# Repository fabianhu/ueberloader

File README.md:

# ueberloader

A RC Battery Charger with high power output and quite small footprint.

Capable of charging 6S at 10A with 24V power supply.

Core component is a "full bridge converter" which is controlled via software.

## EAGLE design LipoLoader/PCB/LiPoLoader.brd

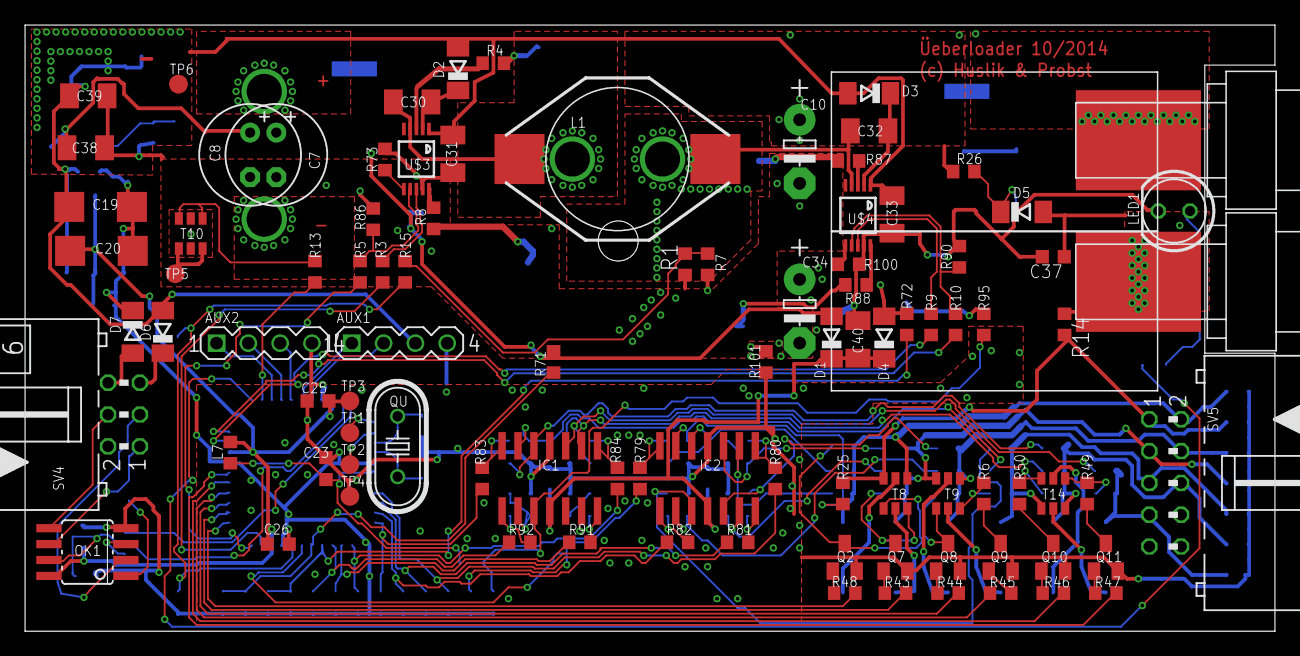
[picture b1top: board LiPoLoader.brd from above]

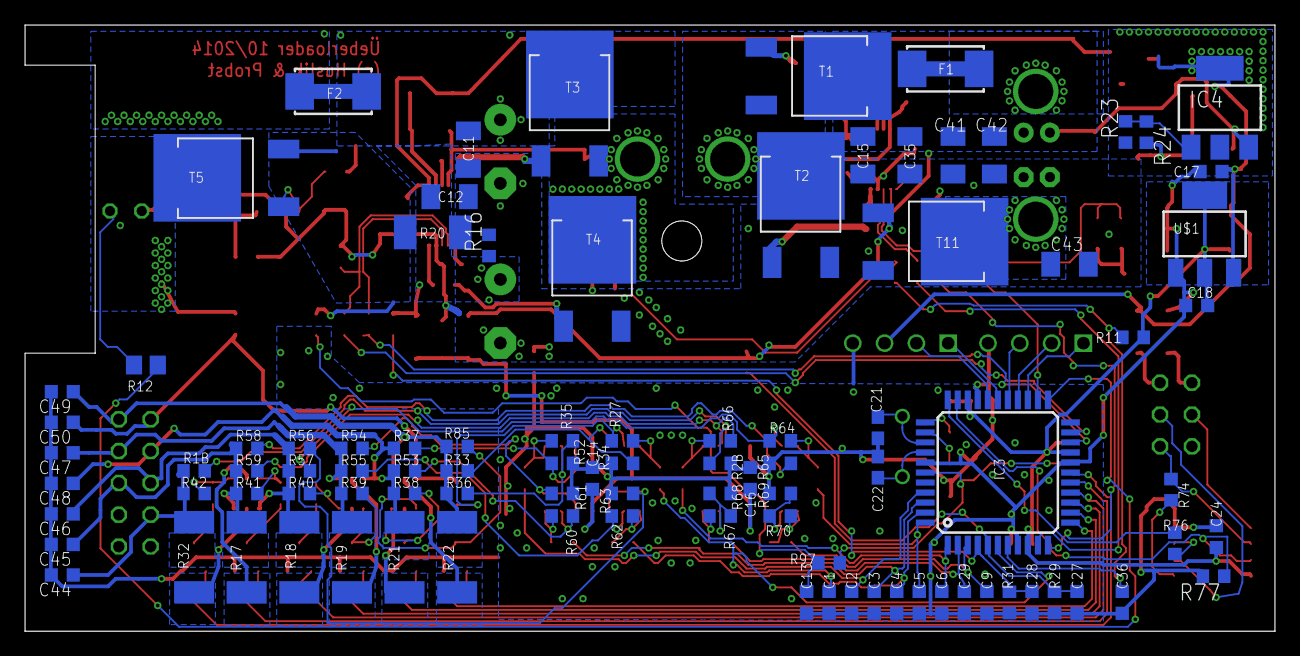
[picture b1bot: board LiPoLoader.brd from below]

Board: 2 copper layers, 99.8 x 48.4 mm, 195 parts (95 on the bottom side), 129 nets.

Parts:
AUX1: aux; MA04-1
AUX2: encoder; MA04-1
C1, C2, C3, C4, C5, C6, C9, C13, C14, C16, C17, C18, C23, C24, C25, C26, C27, C28, C29, C36, C37, C44, C45, C46, C47, C48, C49, C50: 100n; C0603K
C7, C8: 330µF / 25V; E3,5-8
C10, C34: 1000µF/35V; E5-13-L
C11, C15, C30, C31, C32, C33, C38, C39, C40: 1u; C1206K
C12, C35, C41, C42, C43: 10µF; C1206K
C19, C20: 100u Tan; SMC_C
C21, C22: 10p; C0603
COIL1, COIL2: SOLPAD3MM
D1, D2, D3, D4, D6, D7: LL43-GS08; SOD80C
D5: 15V BZT55C15; SOD80C
F1, F2: Fuse 10A; WSC2515
IC1, IC2: LM224D; SO14
IC3: AVR_XMEGA_A4_44A; TQFP44
IC4: LM317MSTT3; SOT223
L1: COILCRAFT_D333; D333
L7: 27nH; R0603
LED1: LED5MM
OK1: ILD217; SOIC08
Q2, Q7, Q8, Q9, Q10, Q11: BC817-25SMD; SOT23-BEC
QU: 16MHz; HC49U-V
R1, R11, R14: 2k2; R0603
R1B, R25, R33, R36, R37, R53, R54, R55, R56, R57, R58, R59: 43k - 0.1%; R0603
R2B, R27, R34, R35, R52, R60, R61, R62, R63, R64, R65, R66: 20k - 0.1%; R0603
R3, R5, R9, R10, R13, R15, R101: 0R; R0603
R4, R8, R87, R88: 10; R0603
R6, R16, R38, R39, R40, R41, R42, R49, R50, R73, R79, R80, R81, R82, R83, R84, R85, R86, R90, R91, R92, R100: 10k; R0603
R7: NB12K00103JBB; R0603
R12: 330; R0805
R17, R18, R19, R21, R22, R32: 10; R2512
R20: 0.005R; R2010
R23: 470; R0603
R24: 3300; R0603
R26: 100k; R0603
R29, R31, R67: 10k - 0.1%; R0603
R43, R44, R45, R46, R47, R48, R77: 4k7; R0603
R68, R69, R95: 2k - 0.1%; R0603
R70: 36k - 0.1%; R0603
R71, R72, R97: 120k - 0.1%; R0603
R74, R76: 820; R0603
SUPP+: SOLPAD3MM
SUPP-: SOLPAD3MM
SV4: comm; ML6L
SV5: ML10L
T1, T2, T3, T4, T5, T11: MOSFET-NIRLR8743; DPAK
T8, T9, T14: QS6J1=FDC6312P; SUPERSOT-6
T10: FDC6401N; SUPERSOT-6
TP1, TP2, TP3, TP4, TP5, TP6: TPTP15R; TP15R
U$1: LM1117; SOT223
U$2: GEH_FISCHER_AKG55XX100_BODEN
U$3, U$4: LM5106; MSOP10W
U$5, U$6: BUCHSE4MM; BUCHSE4MML

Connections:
0V: C7.-, C8.-, C10.-, C11.1, C12.2, C15.1, C31.1, C33.1, C34.-, C35.2, C37.2, C38.1, C39.1, C40.1, C41.2, C42.2, C43.2, LED1.K, R1.1, R7.1, R16.2, R20.1, R24.2, R73.2, R86.2, R90.2, R100.2, R101.2, T2.3, T4.3, T10.P$2, T10.P$5, T11.3, U$3.9, U$4.9
+3V3: C18.2, C20.+, C24.2, C25.2, C26.2, IC3.9, IC3.19, IC3.31, L7.2, OK1.8, R11.2, TP3.TP, U$1.MID, U$1.TAP
+12V: AUX1.3, C17.2, C19.+, C31.2, C33.2, C39.2, D2.A, D3.A, D6.A, IC4.4, R23.1, TP6.TP, U$1.RIGHT, U$3.1, U$4.1
+UB: C10.+, C11.2, C12.1, C34.+, D4.A, F2.1, R16.1, R26.1, R72.1, T3.4
AVCC: C23.2, IC3.39, L7.1, R97.1
BALANCE1: IC3.12, R48.1
BALANCE2: IC3.13, R43.1
BALANCE3: IC3.14, R44.1
BALANCE4: IC3.15, R45.1
BALANCE5: IC3.16, R46.1
BALANCE6: IC3.17, R47.1
BATT-: C37.1, D5.A, R14.1, T5.4, U$6.P$1
BATT-B: R20.2, R95.2, T5.3
BUS_RX: OK1.2, SV4.3
BUS_SUPP: OK1.6, R74.1, SV4.1
BUS_TX: OK1.5, SV4.4
CELL1: C49.1, R22.1, R33.1, R36.1, R85.2, SV5.2, T8.P$4
CELL2: C48.1, R21.1, R37.1, R38.2, R53.1, SV5.3, T9.P$6
CELL3: C47.1, R19.1, R39.2, R54.1, R55.1, SV5.4, T9.P$4
CELL4: C46.1, R18.1, R40.2, R56.1, R57.1, SV5.5, T14.P$4
CELL5: C45.1, R17.1, R41.2, R58.1, R59.1, SV5.6, T14.P$6
CELL6: C44.1, R1B.1, R32.1, R42.2, SV5.7
CELLGND: C50.1, R14.2, R25.1, SV5.1, T8.P$6
GND: AUX1.4, AUX2.4, C1.1, C2.1, C3.1, C4.1, C5.1, C6.1, C9.1, C13.1, C14.1, C16.1, C17.1, C18.1, C19.-, C20.-, C21.1, C22.1, C23.1, C24.1, C25.1, C26.1, C27.1, C28.1, C29.1, C36.1, C44.2, C45.2, C46.2, C47.2, C48.2, C49.2, C50.2, D7.C, IC1.11, IC2.11, IC3.8, IC3.18, IC3.30, IC3.38, IC3.40, OK1.4, Q2.E, Q7.E, Q8.E, Q9.E, Q10.E, Q11.E, R2B.1, R29.2, R31.2, R34.1, R52.1, R61.1, R63.1, R65.1, R68.2, R69.2, R77.2, R101.1, TP4.TP, U$1.LEFT
I_ACT_HI: C9.2, IC3.3, R92.1
I_ACT_LOW: C29.2, IC3.2, R91.1
I_RAW_HI_R: C13.2, IC1.3, R95.1, R97.2
LED1: IC3.23, R12.1
MISO: AUX2.2, IC3.26
MOSI: AUX2.1, IC3.25
unnamed: IC1.10, R1B.2, R2B.2
unnamed: IC1.12, R58.2, R65.2
unnamed: IC1.9, R59.2, R66.2
unnamed: R8.1, T2.1
unnamed: R87.2, U$4.3
unnamed: IC1.13, R57.2, R64.2
unnamed: IC1.6, R67.2, R68.1
unnamed: R100.1, U$4.6
unnamed: OK1.3, R76.1
unnamed: IC2.3, R56.2, R63.2
unnamed: IC2.2, R55.2, R62.2
unnamed: R88.1, T4.1
unnamed: F2.2, U$5.P$1
unnamed: R4.2, U$3.3
unnamed: IC2.5, R54.2, R61.2
unnamed: IC2.6, R53.2, R60.2
unnamed: IC2.12, R33.2, R34.2
unnamed: D7.A, SV4.6
unnamed: LED1.A, R12.2
unnamed: IC2.10, R37.2, R52.2
unnamed: IC2.9, R35.2, R36.2
unnamed: IC2.13, R25.2, R27.2
unnamed: OK1.1, R74.2
unnamed: C32.1, COIL2.P$1, L1.2, T3.3, T4.4, U$4.4
unnamed: R22.2, T8.P$5
unnamed: IC4.1, R23.2, R24.1
unnamed: IC1.2, R69.1, R70.2
unnamed: IC1.8, R66.1, R84.2
unnamed: C21.2, IC3.36, QU.2
unnamed: C22.2, IC3.37, QU.1
unnamed: T10.P$4, T10.P$6, TP5.TP
unnamed: IC1.7, R67.1, R91.2
unnamed: C30.1, COIL1.P$1, L1.1, T1.3, T2.4, U$3.4
unnamed: F1.2, SUPP+.P$1
unnamed: D5.C, R26.2, T5.1
unnamed: Q8.C, R39.1, T9.P$1
unnamed: Q9.C, R6.1
unnamed: R5.2, R86.1, U$3.7
unnamed: R9.1, U$4.8
unnamed: R13.2, T10.P$1, T10.P$3
unnamed: R21.2, T8.P$2
unnamed: R19.2, T9.P$5
unnamed: IC1.14, R64.1, R83.2
unnamed: R18.2, T9.P$2
unnamed: R17.2, T14.P$2
unnamed: R32.2, T14.P$5
unnamed: Q2.C, R85.1, T8.P$1
unnamed: Q7.B, R43.2
unnamed: Q8.B, R44.2
unnamed: Q9.B, R45.2
unnamed: Q10.B, R46.2
unnamed: Q11.B, R47.2
unnamed: IC2.1, R62.1, R82.2
unnamed: R6.2, R40.1, T9.P$3
unnamed: R41.1, R50.2, T14.P$3
unnamed: R42.1, R49.2, T14.P$1
unnamed: Q7.C, R38.1, T8.P$3
unnamed: IC2.7, R60.1, R81.2
unnamed: Q11.C, R49.1
unnamed: Q10.C, R50.1
unnamed: IC2.8, R35.1, R80.2
unnamed: IC2.14, R27.1, R79.2
unnamed: R1.2, R7.2, R15.1
unnamed: R8.2, U$3.10
unnamed: R4.1, T1.1
unnamed: R3.2, U$3.8
unnamed: R73.1, U$3.6
unnamed: C30.2, D2.C, U$3.2
unnamed: IC1.1, R70.1, R92.2
unnamed: R88.2, U$4.10
unnamed: R87.1, T3.1
unnamed: R10.1, R90.1, U$4.7
unnamed: C32.2, D3.C, U$4.2
unnamed: D6.C, SV4.5
unnamed: Q2.B, R48.2
OPAMP_SUPP: C14.2, C16.2, C40.2, D1.C, D4.C, IC1.4, IC2.4
PDI_CLK: IC3.35, TP2.TP
PDI_DATA: IC3.34, TP1.TP
PO1: IC3.24, R13.1
PWM1: IC3.10, R3.1
PWM1EN: IC3.11, R5.1
PWM2: IC3.20, R9.2
PWM2EN: IC3.21, R10.2
SCK: AUX2.3, IC3.27
SCL: AUX1.2, IC3.29
SDA: AUX1.1, IC3.28
SERIAL_RX: IC3.32, OK1.7, R77.1
SERIAL_TX: IC3.33, R76.2
SUPP+: C7.+, C8.+, C15.2, C35.1, C38.2, C41.1, C42.1, D1.A, F1.1, IC4.3, R71.1, T1.4, T11.1
SUPP-A: C43.1, SUPP-.P$1, T11.4
TEMP_MEAS2: C36.2, IC3.7, R11.1, R15.2
U_BATT_MEAS: C28.2, IC3.4, R31.1, R72.2
U_CELL_M1: C1.2, IC3.6, R79.1
U_CELL_M2: C2.2, IC3.41, R80.1
U_CELL_M3: C3.2, IC3.42, R81.1
U_CELL_M4: C4.2, IC3.43, R82.1
U_CELL_M5: C5.2, IC3.44, R83.1
U_CELL_M6: C6.2, IC3.1, R84.1
U_SUPP_MEAS: C27.2, IC3.5, R29.1, R71.2

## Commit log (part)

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2010-08-08 updated PCBs for stackable charger and display
2010-08-09 updated PCBs
2010-08-09 Display um 0.5mm verschoben
2010-08-14 menu.c Änderungen
2010-08-15 fiddling around with touchpad (not working)
2010-10-01 changed OS to "ISR transparent"
2010-10-05 add Jörgs changes Update PCB
2010-10-05 merged joergs changes
2010-10-05 after testing
2010-10-12 add treebuilder for menu
2010-10-13 slightly optimized treebuilder
2010-10-14 minor menue issue after action
2010-10-14 some changes for treebuilder
2010-10-16 optimized treebuilder
2010-10-18 added first autogenerated menu
2010-10-18 finalized treebuilder to a usable state.
2010-10-19 added action prototypes
2010-10-19 fixed small bug and added binary
2010-10-19 implement menu from generator and generator source
2010-10-19 directory operations
2010-10-19 menue testing
2010-10-19 treebuilder test
2010-10-26 Menüstruktur in menu.c manuell berichtigt!
2010-10-26 hopefully fixed the treebuilder
2010-10-26 updated built Treebuilder.exe
2010-11-04 slider geht ganz gut
2010-11-09 somehow small changes to OS ("STS" issue not yet solved)
2010-11-09 some really minor changes the "Timer issue" still persists.
2010-11-24 should be better with newer compiler.
2010-11-24 files gelöscht, die irrtümlich waren ;-)
2010-12-04 fixed DMA error - finally
2010-12-04 minor adjustments to OS
2010-12-04 added comment
2010-12-04 removed include
2010-12-04 renamed global variable
2010-12-04 undo test switch-offs remove "naked" from OS Tasks, because they really NEED a valid stack frame.
2010-12-04 save project settings
2010-12-05 fixed overload/timing issue with display task
2010-12-05 fixed some stuff with timing and init of OS
2011-01-01 new slide algo, but not yet working
2011-01-11 vor grossem Umbenennen
2011-01-11 scheint zu gehen ;-)
2011-01-11 jaa uli geht jetzt
2011-01-16 minor Aufräumaktion
2011-01-16 updated casing
2011-01-18 gestures gehen jetzt richtig.
2011-01-18 scheint zu gehen
2011-01-25 Uli sagt: Zur Not könnten wir das vorerst mal so lassen.
2011-01-25 Ein bis zwei dimensionen besser als vorher
2011-01-31 menu eingehängt, geht aber nur zum Teil.
2011-02-02 Jörg war da und nichts geht mehr...
2011-02-10 geht brauchbar, sagt Uli
2011-02-10 updated treebuilder with stepsize
2011-02-10 updated menu to first integrated (and quite usable) state
2011-02-14 added parameter external definition to header part
2011-02-14 uli war da großer Umbau ohne tiefen Effekt
2011-02-21 zeugs zum Übertrag
2011-02-21 irgendwie besser, aber es lädt nicht
2011-02-21 irgendwie besser, aber lädt nicht.
2011-03-07 kommunikation besser
2011-03-07 safe to eeprom works
2011-03-08 etwas aufgeräumt
2011-03-13 updated treebuilder and convert to VS 10
2011-03-13 changed protocol; mode no more included.
2011-03-13 added action transfer master to slave
2011-03-13 besser jetzt oder?
2011-03-23 hw updates vom Papier
2011-03-23 übertragen des Spannungssollwertes
2011-03-23 most of it is working
2011-04-11 Frequenz einstellbar
2011-04-11 removed instrumentation
2011-04-16 added overall voltage setpoint parameter
2011-04-16 fixed overflow before 32bit calc
2011-05-21 Layout geändert, jetzt passt auch die LED rein
2011-06-22 fixed comm error - finally and fixed to winavr20100110
2011-06-24 with internal reset reason logging softened the reset criteria
2011-08-03 diverses zeugs
2011-08-03 nun mit Änderung des Ladestroms während "Idle"
2011-08-03 toucht testing ON
2011-08-03 ulis version, sliden geht immer noch nicht.
2011-08-16 adjust power reduction register delay charge mode after connect / disconnect.
2011-08-16 added touchdisableslide macro
2011-08-16 new way of adjusting current while charge
2011-08-16 advanced filter (10% filter, more direct) stop on "mode stop" also while charging.
2011-10-27 dxf gehäuse hinzu
2011-10-27 Tastensperre hinzu
2011-11-07 added battery sim
2011-11-13 serial.h actions neu
2011-11-13 changed xml-format for treebuilder (indent)
2011-11-13 first try of calibration
2011-11-14 kalibrierung geht
2011-11-14 falsche defines geändert
2011-11-16 changed base calibration to expect 1.1050 V before new governor;
2011-11-19 Governor working ; Adjust parameters still necessary!
2011-11-19 linewriter in locked state
2011-11-20 linewriter in locked state advanced
2011-11-20 Regler wieder wie er war. I regler, sollwert wegen Spannung verbiegen.
2011-11-21 Neues Menü für Uli. Ein Gechenk.
2011-11-21 Stromregler zweikreisig mit PID
2011-11-21 mit pull-down, dass besser geht.
2011-11-21 Treebuilder mit besserem Layout
2011-12-03 increased menu lines
2012-01-05 added case drawing pdf
2012-02-16 Spule in die BOM
2012-02-16 Regler: Übergangsbereich besser
2012-05-13 removed superfluous file
2012-05-13 minor changes (comments)
2012-05-13 added calibration save and restore; minimal cleanup
2012-05-13 working calibration to and from eeprom
2012-05-15 added todo comments and synced crc.h/c
2012-05-15 a lot of relocations and changes... see the FIXME keyword for remaining stuff
2012-05-15 some cleanup
2012-05-15 clean up more
2012-05-16 seems ok for the display
2012-05-16 hardware comment added
2012-05-16 fixed the balancer
2012-05-16 minor display optimisations
2012-05-16 fixed balancer charge counting
2012-05-17 now the balancer works. Kann sein, dass es etwas dauert, bis die Batterie feritg geladen ist, da erst der Balancer fertig sein muss (15 Zyklen ohne Balancieren)
2012-05-17 changed filter values for balancer measurement
2012-05-17 messung des Balancer nun VIEL besser
2012-05-17 some hardware remarks.
2012-05-17 reduced balancer filter to 1/8
    reduced minimum current while balancing to 30mA
2012-05-18 worked on todo list; check for reference precision!
2012-05-18 updated bom.ods
2012-05-18 UNTESTED Balancer optimisation (end of Balancing)
2012-05-18 emstop langsamer und Überspannungserkennung abh von der Zellenzahl
2012-05-18 Zellen nun von 1-6
2012-05-20 emstop blinken langsamer; kommentare hinzu
2013-08-06 added the changes, which were missing from last backup
2013-08-13 save to eeprom at start of charge; do not begin charge at missing cell changed presets menue emergency stop with auto reset
2013-08-20 added hex files
2013-09-14 added new define for parameter count (needed in FCM)
2013-10-10 Ladestromverstellung Dirty Harry äh Hack
2013-10-17 changed font in Treebuilder.exe
2014-01-03 optimize eeprom save 1/2
2014-01-03 optimize eeprom save 1.5/2
2014-01-07 Added description field (still able to read the old XML)
2014-01-07 beautified Treebuilder.exe
2014-01-07 beautified Treebuilder.exe II
2014-01-08 added Generation UID
2014-02-09 removed unused CRC.
2014-03-21 added comments to fix
2014-04-13 minor fixes and Ulis hack working again
2014-04-14 Verbessertes Verhalten des Touchpads beim Gerätestart
2014-04-16 added readme
2014-04-19 -Ladestromverstellung-Hack -Tastenauswertung verbessert -bleibt ganz gern mal hängen
2014-04-19 fixed data types
2014-04-19 Dieser Kommentar gehört eigentlich zur Rev vorher: Der Stack vom Touch wurde von 300 auf 400 geändert. Jetzt läuft alles sehr gut, auch die Parameter verändern sich beim flashen nicht mehr, lag auch 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
2014-04-19 Tasten umgebaut, reagieren jetzt auf loslassen. Netter Nebeneffekt den ich nicht erklären kann, wenn man eine Taste gedrückt hält, läuft der Wert.
2014-04-19 Gestenerkennung funktioniert referenzmäßig
2014-04-20 noch viel besser, Gesten funktionieren jetzt im ganzen Menü
2014-04-20 plus move
2014-04-21 Move jetzt zeitabhängig. --> Volle Funktionalität erreicht Habe TOUCHMINSIGNAL von 32 auf 20 gestellt. Könnte evtl. zu empfindlich sein und evtl. sich auf anderer HW anders verhalten. Sonst Code aufg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
2014-04-21 bugfix, es wurde manchmal move statt Taste erkannt
2014-04-27 Beim umschalten von mAh auf Ah, Anzeige verbessert - untested Anzeige Supply undervoltage geändert - geht nicht MaxTime und MaxCap implementiert - geht auch nicht Variable für MaxCap von 32 bit auf 1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
2014-04-27 irgendwie kommt das Display mit anzeigen nicht nach, die Ladezeit läuft ungleichmäßig? MaxCap, MaxTime, SupplyVoltage funktionierern
2014-04-30 Anzeige geht supi
2014-04-30 noch besser
2014-05-02 renamed public buffers.
2014-05-06 Ulis rework
2014-08-31 Max. Time in Minuten, Einheiten von Ladestrom und so wurden in Auto-Generierten Code reingehackt. Treebuilder anpassen!!
2014-08-31 ulis text-hack gefixt
2014-09-27 -Strommessung high Range misst jetzt richtig - Gesamtakkuspannung stimmt jetzt viel besser
2014-09-28 Low-Range Strommessung wurde deaktiviert, da Hight Range im unteren Bereich jetzt perfekt misst. Das obere Ende der Strommessung sollte Laderindividuell calibrierbar werden. (Bauteiltoleranzen) Bei e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
2014-10-19 removed low range measurement from PCB/LiPoLoader.sch (with eagle 5.12 !)
2015-01-02 Tastenentprellung eingebaut
2015-10-18 converted to eagle 7.3
2016-05-29 Viele Kleinigkeiten geändert: -es gibt mehr Presets und sie lassen sich jetzt abspeichern -Abschaltverhalten verändert -Logik für laden ohne Balancer angepasst -KI-Wert des Soll-Ladestroms von 8000 a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
2017-03-25 Create LICENSE
